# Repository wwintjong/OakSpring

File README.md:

# keyboard_tkl
 A tenkeyless (TKL) or 80% style keyboard powered with Raspberry Pi's 2040. The keyboard is hot-swappable and has LED backlight on individual keys.

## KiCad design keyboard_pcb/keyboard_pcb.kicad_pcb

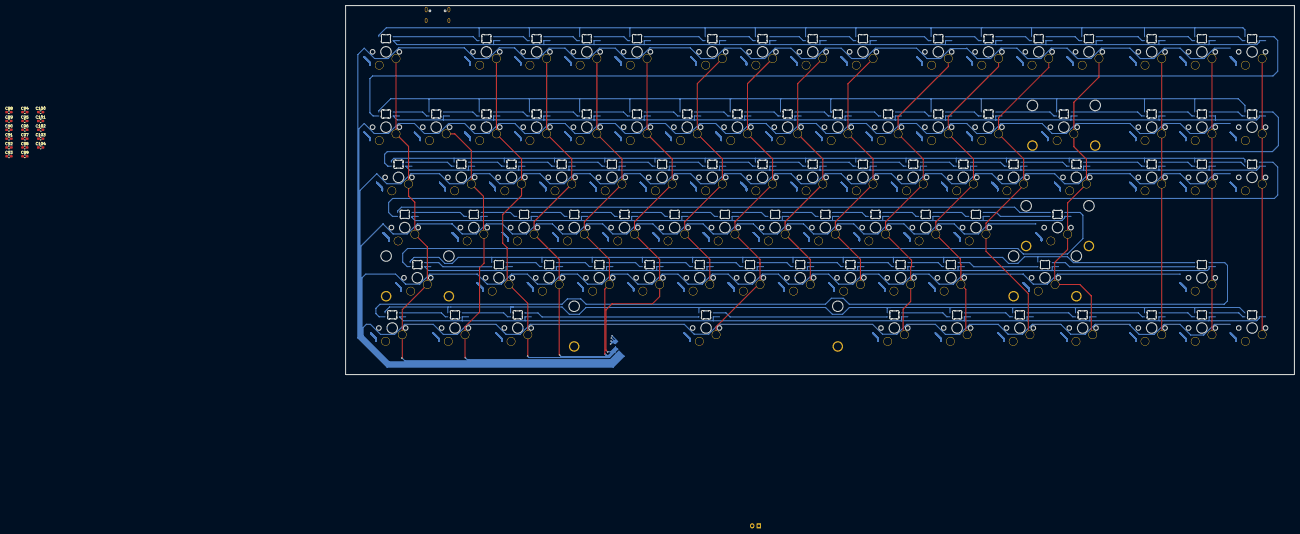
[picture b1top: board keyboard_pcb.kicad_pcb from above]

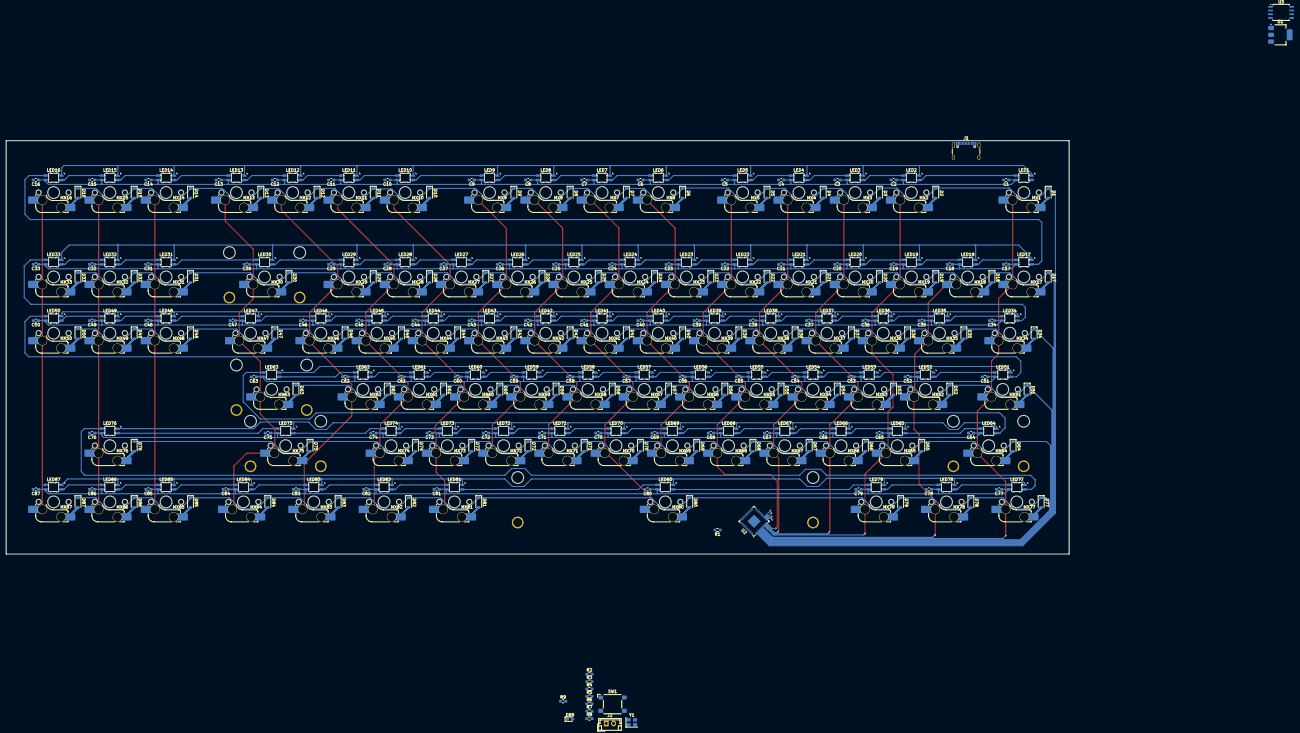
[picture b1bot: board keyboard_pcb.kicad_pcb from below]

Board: 2 copper layers, 360.0 x 140.0 mm, 387 parts (365 on the bottom side), 221 nets.

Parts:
C1, C2, C3, C4, C5, C6, C7, C8, C9, C10, C11, C12, C13, C14, C15, C16, C17, C18, C19, C20, C21, C22, C23, C24, C25, C26, C27, C28, C29, C30, C31, C32, C33, C34, C35, C36, C37, C38, C39, C40, C41, C42, C43, C44, C45, C46, C47, C48, C49, C50, C51, C52, C53, C54, C55, C56, C57, C58, C59, C60, C61, C62, C63, C64, C65, C66, C67, C68, C69, C70, C71, C72, C73, C74, C75, C76, C77, C78, C79, C80, C81, C82, C83, C84, C85, C86, C87, C88, C89, C90, C91, C92, C93, C94, C95, C96, C100, C104: 100nF; C_0603_1608Metric_Pad1.08x0.95mm_HandSolder
C97, C98: 1uF; C_0603_1608Metric_Pad1.08x0.95mm_HandSolder
C99, C101: 10u; C_0603_1608Metric_Pad1.08x0.95mm_HandSolder
C102, C103: 30pF; C_0603_1608Metric_Pad1.08x0.95mm_HandSolder
D1, D2, D3, D4, D5, D6, D7, D8, D9, D10, D11, D12, D13, D14, D15, D16, D17, D18, D19, D20, D21, D22, D23, D24, D25, D26, D27, D28, D29, D30, D31, D32, D33, D34, D35, D36, D37, D38, D39, D40, D41, D42, D43, D44, D45, D46, D47, D48, D49, D50, D51, D52, D53, D54, D55, D56, D57, D58, D59, D60, D61, D62, D63, D64, D65, D66, D67, D68, D69, D70, D71, D72, D73, D74, D75, D76, D77, D78, D79, D80, D81, D82, D83, D84, D85, D86, D87: D; D_SOD-123
D88: LED; LED_0603_1608Metric_Pad1.05x0.95mm_HandSolder
J1: USB_C_Receptacle_USB2.0_16P; USB_C_Receptacle_GCT_USB4105-xx-A_16P_TopMnt_Horizontal
J2: Conn_01x02; JST_EH_B2B-EH-A_1x02_P2.50mm_Vertical
LED1, LED2, LED3, LED4, LED5, LED6, LED7, LED8, LED9, LED10, LED11, LED12, LED13, LED14, LED15, LED16, LED17, LED18, LED19, LED20, LED21, LED22, LED23, LED24, LED25, LED26, LED27, LED28, LED29, LED30, LED31, LED32, LED33, LED34, LED35, LED36, LED37, LED38, LED39, LED40, LED41, LED42, LED43, LED44, LED45, LED46, LED47, LED48, LED49, LED50, LED51, LED52, LED53, LED54, LED55, LED56, LED57, LED58, LED59, LED60, LED61, LED62, LED63, LED64, LED65, LED66, LED67, LED68, LED69, LED70, LED71, LED72, LED73, LED74, LED75, LED76, LED77, LED78, LED79, LED80, LED81, LED82, LED83, LED84, LED85, LED86, LED87: MX_SK6812MINI-E; LED_MX_6028R
MX1, MX2, MX3, MX4, MX5, MX6, MX7, MX8, MX9, MX10, MX11, MX12, MX13, MX14, MX15, MX16, MX17, MX18, MX19, MX20, MX21, MX22, MX23, MX24, MX25, MX26, MX27, MX28, MX29, MX30, MX31, MX32, MX33, MX34, MX35, MX36, MX37, MX38, MX39, MX40, MX41, MX42, MX43, MX44, MX45, MX46, MX47, MX48, MX49, MX50, MX51, MX52, MX53, MX54, MX55, MX56, MX57, MX58, MX59, MX60, MX61, MX62, MX63, MX64, MX65, MX66, MX67, MX68, MX69, MX70, MX71, MX72, MX73, MX74, MX75, MX76, MX77, MX78, MX79, MX80, MX81, MX82, MX83, MX84, MX85, MX86, MX87: MX_SW_HS; SW_MX_HS_CPG151101S11_1u
R1: R; R_0603_1608Metric_Pad0.98x0.95mm_HandSolder
R2, R4: 27; R_0603_1608Metric_Pad0.98x0.95mm_HandSolder
R3, R5: 5.1k; R_0603_1608Metric_Pad0.98x0.95mm_HandSolder
R6, R7: 1k; R_0603_1608Metric_Pad0.98x0.95mm_HandSolder
R8: 470; R_0603_1608Metric_Pad0.98x0.95mm_HandSolder
R9: 300; R_0603_1608Metric_Pad0.98x0.95mm_HandSolder
S1: MX_stab; STAB_MX_P_2u
S2, S4: MX_stab; STAB_MX_P_2.25u
S3: MX_stab; STAB_MX_P_2.75u
S5: MX_stab; STAB_MX_P_6.25u
SW1: Reset; SW_SPST_Omron_B3FS-100xP
U1: NCP1117-3.3_SOT223; SOT-223-3_TabPin2
U2: RP2040; QFN-56-1EP_7x7mm_P0.4mm_EP3.2x3.2mm
U3: W25Q128JVS; SOIC-8_5.23x5.23mm_P1.27mm
Y1: Crystal_GND24; Crystal_SMD_Abracon_ABM8G-4Pin_3.2x2.5mm

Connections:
+1V1: C88.1, C89.1, C98.2, U2.23 (DVDD), U2.45 (VREG_VOUT), U2.50 (DVDD)
+3V3: C90.1, C91.1, C92.1, C93.1, C94.1, C95.1, C96.1, C97.1, C101.1, C104.1, D88.2 (A), R1.1, U1.2 (VO), U2.1 (IOVDD), U2.10 (IOVDD), U2.22 (IOVDD), U2.33 (IOVDD), U2.42 (IOVDD), U2.43 (ADC_AVDD), U2.44 (VREG_IN), U2.48 (USB_VDD), U2.49 (IOVDD), U3.8 (VCC)
+5V: C1.1, C2.1, C3.1, C4.1, C5.1, C6.1, C7.1, C8.1, C9.1, C10.1, C11.1, C12.1, C13.1, C14.1, C15.1, C16.1, C17.1, C18.1, C19.1, C20.1, C21.1, C22.1, C23.1, C24.1, C25.1, C26.1, C27.1, C28.1, C29.1, C30.1, C31.1, C32.1, C33.1, C34.1, C35.1, C36.1, C37.1, C38.1, C39.1, C40.1, C41.1, C42.1, C43.1, C44.1, C45.1, C46.1, C47.1, C48.1, C49.1, C50.1, C51.1, C52.1, C53.1, C54.1, C55.1, C56.1, C57.1, C58.1, C59.1, C60.1, C61.1, C62.1, C63.1, C64.1, C65.1, C66.1, C67.1, C68.1, C69.1, C70.1, C71.1, C72.1, C73.1, C74.1, C75.1, C76.1, C77.1, C78.1, C79.1, C80.1, C81.1, C82.1, C83.1, C84.1, C85.1, C86.1, C87.1, LED1.1 (VDD), LED2.1 (VDD), LED3.1 (VDD), LED4.1 (VDD), LED5.1 (VDD), LED6.1 (VDD), LED7.1 (VDD), LED8.1 (VDD), LED9.1 (VDD), LED10.1 (VDD), LED11.1 (VDD), LED12.1 (VDD), LED13.1 (VDD), LED14.1 (VDD), LED15.1 (VDD), LED16.1 (VDD), LED17.1 (VDD), LED18.1 (VDD), LED19.1 (VDD), LED20.1 (VDD), LED21.1 (VDD), LED22.1 (VDD), LED23.1 (VDD), LED24.1 (VDD), LED25.1 (VDD), LED26.1 (VDD), LED27.1 (VDD), LED28.1 (VDD), LED29.1 (VDD), LED30.1 (VDD), LED31.1 (VDD), LED32.1 (VDD), LED33.1 (VDD), LED34.1 (VDD), LED35.1 (VDD), LED36.1 (VDD), LED37.1 (VDD), LED38.1 (VDD), LED39.1 (VDD), LED40.1 (VDD), LED41.1 (VDD), LED42.1 (VDD), LED43.1 (VDD), LED44.1 (VDD), LED45.1 (VDD), LED46.1 (VDD), LED47.1 (VDD), LED48.1 (VDD), LED49.1 (VDD), LED50.1 (VDD), LED51.1 (VDD), LED52.1 (VDD), LED53.1 (VDD), LED54.1 (VDD), LED55.1 (VDD), LED56.1 (VDD), LED57.1 (VDD), LED58.1 (VDD), LED59.1 (VDD), LED60.1 (VDD), LED61.1 (VDD), LED62.1 (VDD), LED63.1 (VDD), LED64.1 (VDD), LED65.1 (VDD), LED66.1 (VDD), LED67.1 (VDD), LED68.1 (VDD), LED69.1 (VDD), LED70.1 (VDD), LED71.1 (VDD), LED72.1 (VDD), LED73.1 (VDD), LED74.1 (VDD), LED75.1 (VDD), LED76.1 (VDD), LED77.1 (VDD), LED78.1 (VDD), LED79.1 (VDD), LED80.1 (VDD), LED81.1 (VDD), LED82.1 (VDD), LED83.1 (VDD), LED84.1 (VDD), LED85.1 (VDD), LED86.1 (VDD), LED87.1 (VDD)
/Microcontroller/QSPI_SCLK: U2.52 (QSPI_SCLK), U3.6 (CLK)
/Microcontroller/QSPI_SD0: U2.53 (QSPI_SD0), U3.5 (DI(IO0))
/Microcontroller/QSPI_SD1: U2.55 (QSPI_SD1), U3.2 (DO(IO1))
/Microcontroller/QSPI_SD2: U2.54 (QSPI_SD2), U3.3 (IO2)
/Microcontroller/QSPI_SD3: U2.51 (QSPI_SD3), U3.7 (IO3)
/Microcontroller/QSPI_SS: R7.2, U2.56 (QSPI_SS), U3.1 (~CS)
/Microcontroller/Run: C100.1, R1.2, SW1.1
/Microcontroller/USB_BOOT: J2.1, R7.1
/Microcontroller/USB_D+: J1.A6 (D+), J1.B6 (D+), R2.1
/Microcontroller/USB_D-: J1.A7 (D-), J1.B7 (D-), R4.2
/Microcontroller/XIN: C102.2, U2.20 (XIN), Y1.3
/Microcontroller/XOUT: R6.2, U2.21 (XOUT)
GND: C1.2, C2.2, C3.2, C4.2, C5.2, C6.2, C7.2, C8.2, C9.2, C10.2, C11.2, C12.2, C13.2, C14.2, C15.2, C16.2, C17.2, C18.2, C19.2, C20.2, C21.2, C22.2, C23.2, C24.2, C25.2, C26.2, C27.2, C28.2, C29.2, C30.2, C31.2, C32.2, C33.2, C34.2, C35.2, C36.2, C37.2, C38.2, C39.2, C40.2, C41.2, C42.2, C43.2, C44.2, C45.2, C46.2, C47.2, C48.2, C49.2, C50.2, C51.2, C52.2, C53.2, C54.2, C55.2, C56.2, C57.2, C58.2, C59.2, C60.2, C61.2, C62.2, C63.2, C64.2, C65.2, C66.2, C67.2, C68.2, C69.2, C70.2, C71.2, C72.2, C73.2, C74.2, C75.2, C76.2, C77.2, C78.2, C79.2, C80.2, C81.2, C82.2, C83.2, C84.2, C85.2, C86.2, C87.2, C88.2, C89.2, C90.2, C91.2, C92.2, C93.2, C94.2, C95.2, C96.2, C97.2, C98.1, C99.2, C100.2, C101.2, C102.1, C103.1, C104.2, J1.A1 (GND), J1.A12 (GND), J1.B1 (GND), J1.B12 (GND), J1.S1 (SHIELD), J2.2, LED1.4 (VSS), LED2.4 (VSS), LED3.4 (VSS), LED4.4 (VSS), LED5.4 (VSS), LED6.4 (VSS), LED7.4 (VSS), LED8.4 (VSS), LED9.4 (VSS), LED10.4 (VSS), LED11.4 (VSS), LED12.4 (VSS), LED13.4 (VSS), LED14.4 (VSS), LED15.4 (VSS), LED16.4 (VSS), LED17.4 (VSS), LED18.4 (VSS), LED19.4 (VSS), LED20.4 (VSS), LED21.4 (VSS), LED22.4 (VSS), LED23.4 (VSS), LED24.4 (VSS), LED25.4 (VSS), LED26.4 (VSS), LED27.4 (VSS), LED28.4 (VSS), LED29.4 (VSS), LED30.4 (VSS), LED31.4 (VSS), LED32.4 (VSS), LED33.4 (VSS), LED34.4 (VSS), LED35.4 (VSS), LED36.4 (VSS), LED37.4 (VSS), LED38.4 (VSS), LED39.4 (VSS), LED40.4 (VSS), LED41.4 (VSS), LED42.4 (VSS), LED43.4 (VSS), LED44.4 (VSS), LED45.4 (VSS), LED46.4 (VSS), LED47.4 (VSS), LED48.4 (VSS), LED49.4 (VSS), LED50.4 (VSS), LED51.4 (VSS), LED52.4 (VSS), LED53.4 (VSS), LED54.4 (VSS), LED55.4 (VSS), LED56.4 (VSS), LED57.4 (VSS), LED58.4 (VSS), LED59.4 (VSS), LED60.4 (VSS), LED61.4 (VSS), LED62.4 (VSS), LED63.4 (VSS), LED64.4 (VSS), LED65.4 (VSS), LED66.4 (VSS), LED67.4 (VSS), LED68.4 (VSS), LED69.4 (VSS), LED70.4 (VSS), LED71.4 (VSS), LED72.4 (VSS), LED73.4 (VSS), LED74.4 (VSS), LED75.4 (VSS), LED76.4 (VSS), LED77.4 (VSS), LED78.4 (VSS), LED79.4 (VSS), LED80.4 (VSS), LED81.4 (VSS), LED82.4 (VSS), LED83.4 (VSS), LED84.4 (VSS), LED85.4 (VSS), LED86.4 (VSS), LED87.4 (VSS), R3.2, R5.2, R8.2, SW1.2, U1.1 (GND), U2.19 (TESTEN), U2.57 (GND), U3.4 (GND), Y1.2, Y1.4
LED: LED1.3 (DIN), R9.2
unnamed: C103.2, R6.1, Y1.1
unnamed: D1.2 (A), MX1.2
unnamed: D2.2 (A), MX2.2
unnamed: D3.2 (A), MX3.2
unnamed: D4.2 (A), MX4.2
unnamed: D5.2 (A), MX5.2
unnamed: D6.2 (A), MX6.2
unnamed: D7.2 (A), MX7.2
unnamed: D8.2 (A), MX8.2
unnamed: D9.2 (A), MX9.2
unnamed: D10.2 (A), MX10.2
unnamed: D11.2 (A), MX11.2
unnamed: D12.2 (A), MX12.2
unnamed: D13.2 (A), MX13.2
unnamed: D14.2 (A), MX14.2
unnamed: D15.2 (A), MX15.2
unnamed: D16.2 (A), MX16.2
unnamed: D17.2 (A), MX17.2
unnamed: D18.2 (A), MX18.2
unnamed: D19.2 (A), MX19.2
unnamed: D20.2 (A), MX20.2
unnamed: D21.2 (A), MX21.2
unnamed: D22.2 (A), MX22.2
unnamed: D23.2 (A), MX23.2
unnamed: D24.2 (A), MX24.2
unnamed: D25.2 (A), MX25.2
unnamed: D26.2 (A), MX26.2
unnamed: D27.2 (A), MX27.2
unnamed: D28.2 (A), MX28.2
unnamed: D29.2 (A), MX29.2
unnamed: D30.2 (A), MX30.2
unnamed: D31.2 (A), MX31.2
unnamed: D32.2 (A), MX32.2
unnamed: D33.2 (A), MX33.2
unnamed: D34.2 (A), MX34.2
unnamed: D35.2 (A), MX35.2
unnamed: D36.2 (A), MX36.2
unnamed: D37.2 (A), MX37.2
unnamed: D38.2 (A), MX38.2
unnamed: D39.2 (A), MX39.2
unnamed: D40.2 (A), MX40.2
unnamed: D41.2 (A), MX41.2
unnamed: D42.2 (A), MX42.2
unnamed: D43.2 (A), MX43.2
unnamed: D44.2 (A), MX44.2
unnamed: D45.2 (A), MX45.2
unnamed: D46.2 (A), MX46.2
unnamed: D47.2 (A), MX47.2
unnamed: D48.2 (A), MX48.2
unnamed: D49.2 (A), MX49.2
unnamed: D50.2 (A), MX50.2
unnamed: D51.2 (A), MX51.2
unnamed: D52.2 (A), MX52.2
unnamed: D53.2 (A), MX53.2
unnamed: D54.2 (A), MX54.2
unnamed: D55.2 (A), MX55.2
unnamed: D56.2 (A), MX56.2
unnamed: D57.2 (A), MX57.2
unnamed: D58.2 (A), MX58.2
unnamed: D59.2 (A), MX59.2
unnamed: D60.2 (A), MX60.2
unnamed: D61.2 (A), MX61.2
unnamed: D62.2 (A), MX62.2
unnamed: D63.2 (A), MX63.2
unnamed: D64.2 (A), MX64.2
unnamed: D65.2 (A), MX65.2
unnamed: D66.2 (A), MX66.2
unnamed: D67.2 (A), MX67.2
unnamed: D68.2 (A), MX68.2
unnamed: D69.2 (A), MX69.2
unnamed: D70.2 (A), MX70.2
unnamed: D71.2 (A), MX71.2
unnamed: D72.2 (A), MX72.2
unnamed: D73.2 (A), MX73.2
unnamed: D74.2 (A), MX74.2
unnamed: D75.2 (A), MX75.2
unnamed: D76.2 (A), MX76.2
unnamed: D77.2 (A), MX77.2
unnamed: D78.2 (A), MX78.2
unnamed: D79.2 (A), MX79.2
unnamed: D80.2 (A), MX80.2
unnamed: D81.2 (A), MX81.2
unnamed: D82.2 (A), MX82.2
unnamed: D83.2 (A), MX83.2
unnamed: D84.2 (A), MX84.2
unnamed: D85.2 (A), MX85.2
unnamed: D86.2 (A), MX86.2
unnamed: D87.2 (A), MX87.2
unnamed: D88.1 (K), R8.1
unnamed: J1.A5 (CC1), R3.1
unnamed: J1.B5 (CC2), R5.1
unnamed: LED1.2 (DOUT), LED2.3 (DIN)
unnamed: LED2.2 (DOUT), LED3.3 (DIN)
unnamed: LED3.2 (DOUT), LED4.3 (DIN)
unnamed: LED4.2 (DOUT), LED5.3 (DIN)
unnamed: LED5.2 (DOUT), LED6.3 (DIN)
unnamed: LED6.2 (DOUT), LED7.3 (DIN)
unnamed: LED7.2 (DOUT), LED8.3 (DIN)
unnamed: LED8.2 (DOUT), LED9.3 (DIN)
unnamed: LED9.2 (DOUT), LED10.3 (DIN)
unnamed: LED10.2 (DOUT), LED11.3 (DIN)
unnamed: LED11.2 (DOUT), LED12.3 (DIN)
unnamed: LED12.2 (DOUT), LED13.3 (DIN)
unnamed: LED13.2 (DOUT), LED14.3 (DIN)
unnamed: LED14.2 (DOUT), LED15.3 (DIN)
unnamed: LED15.2 (DOUT), LED16.3 (DIN)
unnamed: LED16.2 (DOUT), LED17.3 (DIN)
unnamed: LED17.2 (DOUT), LED18.3 (DIN)
unnamed: LED18.2 (DOUT), LED19.3 (DIN)
unnamed: LED19.2 (DOUT), LED20.3 (DIN)
unnamed: LED20.2 (DOUT), LED21.3 (DIN)
unnamed: LED21.2 (DOUT), LED22.3 (DIN)
unnamed: LED22.2 (DOUT), LED23.3 (DIN)
unnamed: LED23.2 (DOUT), LED24.3 (DIN)
unnamed: LED24.2 (DOUT), LED25.3 (DIN)
unnamed: LED25.2 (DOUT), LED26.3 (DIN)
unnamed: LED26.2 (DOUT), LED27.3 (DIN)
unnamed: LED27.2 (DOUT), LED28.3 (DIN)
unnamed: LED28.2 (DOUT), LED29.3 (DIN)
unnamed: LED29.2 (DOUT), LED30.3 (DIN)
unnamed: LED30.2 (DOUT), LED31.3 (DIN)
unnamed: LED31.2 (DOUT), LED32.3 (DIN)
unnamed: LED32.2 (DOUT), LED33.3 (DIN)
unnamed: LED33.2 (DOUT), LED34.3 (DIN)
unnamed: LED34.2 (DOUT), LED35.3 (DIN)
unnamed: LED35.2 (DOUT), LED36.3 (DIN)
unnamed: LED36.2 (DOUT), LED37.3 (DIN)
unnamed: LED37.2 (DOUT), LED38.3 (DIN)
unnamed: LED38.2 (DOUT), LED39.3 (DIN)
unnamed: LED39.2 (DOUT), LED40.3 (DIN)
unnamed: LED40.2 (DOUT), LED41.3 (DIN)
unnamed: LED41.2 (DOUT), LED42.3 (DIN)
unnamed: LED42.2 (DOUT), LED43.3 (DIN)
unnamed: LED43.2 (DOUT), LED44.3 (DIN)
unnamed: LED44.2 (DOUT), LED45.3 (DIN)
unnamed: LED45.2 (DOUT), LED46.3 (DIN)
unnamed: LED46.2 (DOUT), LED47.3 (DIN)
unnamed: LED47.2 (DOUT), LED48.3 (DIN)
unnamed: LED48.2 (DOUT), LED49.3 (DIN)
unnamed: LED49.2 (DOUT), LED50.3 (DIN)
unnamed: LED50.2 (DOUT), LED51.3 (DIN)
unnamed: LED51.2 (DOUT), LED52.3 (DIN)
unnamed: LED52.2 (DOUT), LED53.3 (DIN)
unnamed: LED53.2 (DOUT), LED54.3 (DIN)
unnamed: LED54.2 (DOUT), LED55.3 (DIN)
unnamed: LED55.2 (DOUT), LED56.3 (DIN)
unnamed: LED56.2 (DOUT), LED57.3 (DIN)
unnamed: LED57.2 (DOUT), LED58.3 (DIN)
unnamed: LED58.2 (DOUT), LED59.3 (DIN)
unnamed: LED59.2 (DOUT), LED60.3 (DIN)
unnamed: LED60.2 (DOUT), LED61.3 (DIN)
unnamed: LED61.2 (DOUT), LED62.3 (DIN)
unnamed: LED62.2 (DOUT), LED63.3 (DIN)
unnamed: LED63.2 (DOUT), LED64.3 (DIN)
unnamed: LED64.2 (DOUT), LED65.3 (DIN)
unnamed: LED65.2 (DOUT), LED66.3 (DIN)
unnamed: LED66.2 (DOUT), LED67.3 (DIN)
unnamed: LED67.2 (DOUT), LED68.3 (DIN)
unnamed: LED68.2 (DOUT), LED69.3 (DIN)
unnamed: LED69.2 (DOUT), LED70.3 (DIN)
unnamed: LED70.2 (DOUT), LED71.3 (DIN)
unnamed: LED71.2 (DOUT), LED72.3 (DIN)
unnamed: LED72.2 (DOUT), LED73.3 (DIN)
unnamed: LED73.2 (DOUT), LED74.3 (DIN)
unnamed: LED74.2 (DOUT), LED75.3 (DIN)
unnamed: LED75.2 (DOUT), LED76.3 (DIN)
unnamed: LED76.2 (DOUT), LED77.3 (DIN)
unnamed: LED77.2 (DOUT), LED78.3 (DIN)
unnamed: LED78.2 (DOUT), LED79.3 (DIN)
unnamed: LED79.2 (DOUT), LED80.3 (DIN)
unnamed: LED80.2 (DOUT), LED81.3 (DIN)
unnamed: LED81.2 (DOUT), LED82.3 (DIN)
unnamed: LED82.2 (DOUT), LED83.3 (DIN)
unnamed: LED83.2 (DOUT), LED84.3 (DIN)
unnamed: LED84.2 (DOUT), LED85.3 (DIN)
unnamed: LED85.2 (DOUT), LED86.3 (DIN)
unnamed: LED86.2 (DOUT), LED87.3 (DIN)
unnamed: R9.1, U2.35 (GPIO23)
unnamed: R4.1, U2.46 (USB_DM)
unnamed: R2.2, U2.47 (USB_DP)
VBUS: C99.1, J1.A4 (VBUS), J1.A9 (VBUS), J1.B4 (VBUS), J1.B9 (VBUS), U1.3 (VI)
col0: MX1.1, MX17.1, MX34.1, MX51.1, MX64.1, MX77.1, U2.8 (GPIO6)
col1: MX18.1, MX35.1, MX52.1, MX78.1, U2.9 (GPIO7)
col2: MX2.1, MX19.1, MX36.1, MX65.1, MX79.1, U2.11 (GPIO8)
col3: MX3.1, MX20.1, MX37.1, MX53.1, MX66.1, U2.12 (GPIO9)
col4: MX4.1, MX21.1, MX38.1, MX54.1, MX67.1, U2.13 (GPIO10)
col5: MX5.1, MX22.1, MX39.1, MX55.1, MX68.1, U2.14 (GPIO11)
col6: MX6.1, MX23.1, MX40.1, MX56.1, MX69.1, U2.15 (GPIO12)
col7: MX7.1, MX24.1, MX41.1, MX57.1, MX70.1, MX80.1, U2.16 (GPIO13)
col8: MX8.1, MX25.1, MX42.1, MX58.1, MX71.1, U2.17 (GPIO14)
col9: MX9.1, MX26.1, MX43.1, MX59.1, MX72.1, U2.18 (GPIO15)
col10: MX10.1, MX27.1, MX44.1, MX60.1, MX73.1, MX81.1, U2.27 (GPIO16)
col11: MX11.1, MX28.1, MX45.1, MX61.1, MX74.1, MX82.1, U2.28 (GPIO17)
col12: MX12.1, MX29.1, MX46.1, MX62.1, MX83.1, U2.29 (GPIO18)
col13: MX13.1, MX30.1, MX47.1, MX63.1, MX75.1, MX84.1, U2.30 (GPIO19)
col14: MX14.1, MX31.1, MX48.1, MX85.1, U2.31 (GPIO20)
col15: MX15.1, MX32.1, MX49.1, MX76.1, MX86.1, U2.32 (GPIO21)
col16: MX16.1, MX33.1, MX50.1, MX87.1, U2.34 (GPIO22)
row0: D1.1 (K), D2.1 (K), D3.1 (K), D4.1 (K), D5.1 (K), D6.1 (K), D7.1 (K), D8.1 (K), D9.1 (K), D10.1 (K), D11.1 (K), D12.1 (K), D13.1 (K), D14.1 (K), D15.1 (K), D16.1 (K), U2.2 (GPIO0)
row1: D17.1 (K), D18.1 (K), D19.1 (K), D20.1 (K), D21.1 (K), D22.1 (K), D23.1 (K), D24.1 (K), D25.1 (K), D26.1 (K), D27.1 (K), D28.1 (K), D29.1 (K), D30.1 (K), D31.1 (K), D32.1 (K), D33.1 (K), U2.3 (GPIO1)
row2: D34.1 (K), D35.1 (K), D36.1 (K), D37.1 (K), D38.1 (K), D39.1 (K), D40.1 (K), D41.1 (K), D42.1 (K), D43.1 (K), D44.1 (K), D45.1 (K), D46.1 (K), D47.1 (K), D48.1 (K), D49.1 (K), D50.1 (K), U2.4 (GPIO2)
row3: D51.1 (K), D52.1 (K), D53.1 (K), D54.1 (K), D55.1 (K), D56.1 (K), D57.1 (K), D58.1 (K), D59.1 (K), D60.1 (K), D61.1 (K), D62.1 (K), D63.1 (K), U2.5 (GPIO3)
row4: D64.1 (K), D65.1 (K), D66.1 (K), D67.1 (K), D68.1 (K), D69.1 (K), D70.1 (K), D71.1 (K), D72.1 (K), D73.1 (K), D74.1 (K), D75.1 (K), D76.1 (K), U2.6 (GPIO4)
row5: D77.1 (K), D78.1 (K), D79.1 (K), D80.1 (K), D81.1 (K), D82.1 (K), D83.1 (K), D84.1 (K), D85.1 (K), D86.1 (K), D87.1 (K), U2.7 (GPIO5)

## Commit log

2025-01-14 added symbol library and footprints
2025-01-15 drew mcu schematic
2025-01-20 implemented matrix
2025-01-21 implemented LEDs and switch and diode layout
2025-01-21 update pcb with LED
2025-01-22 Started routing traces part 1
2025-01-22 starting routing traces part 2
2025-01-22 starting routing traces part 3
2025-01-22 starting routing traces part 4
2025-01-22 starting routing traces part 5
2025-01-22 starting routing traces part 6
2025-01-22 starting routing traces part 7
2025-01-22 starting routing traces part 8
2025-01-23 added led capacitors and route all leds
2025-01-24 restructured schematic
2025-01-24 updated schematic
2025-01-27 started routing mcu
2025-01-28 finished routing traces with mcu
2025-01-28 completed all routing and ground fill
2025-01-30 edited power supply circuits
2025-02-01 reworked board outline
2025-02-03 relocated the mcu to the shoulder
2025-02-03 minor tweaks and gerber file
2025-02-04 README.md
2025-02-04 minor fix
2025-02-04 updated gerber file
